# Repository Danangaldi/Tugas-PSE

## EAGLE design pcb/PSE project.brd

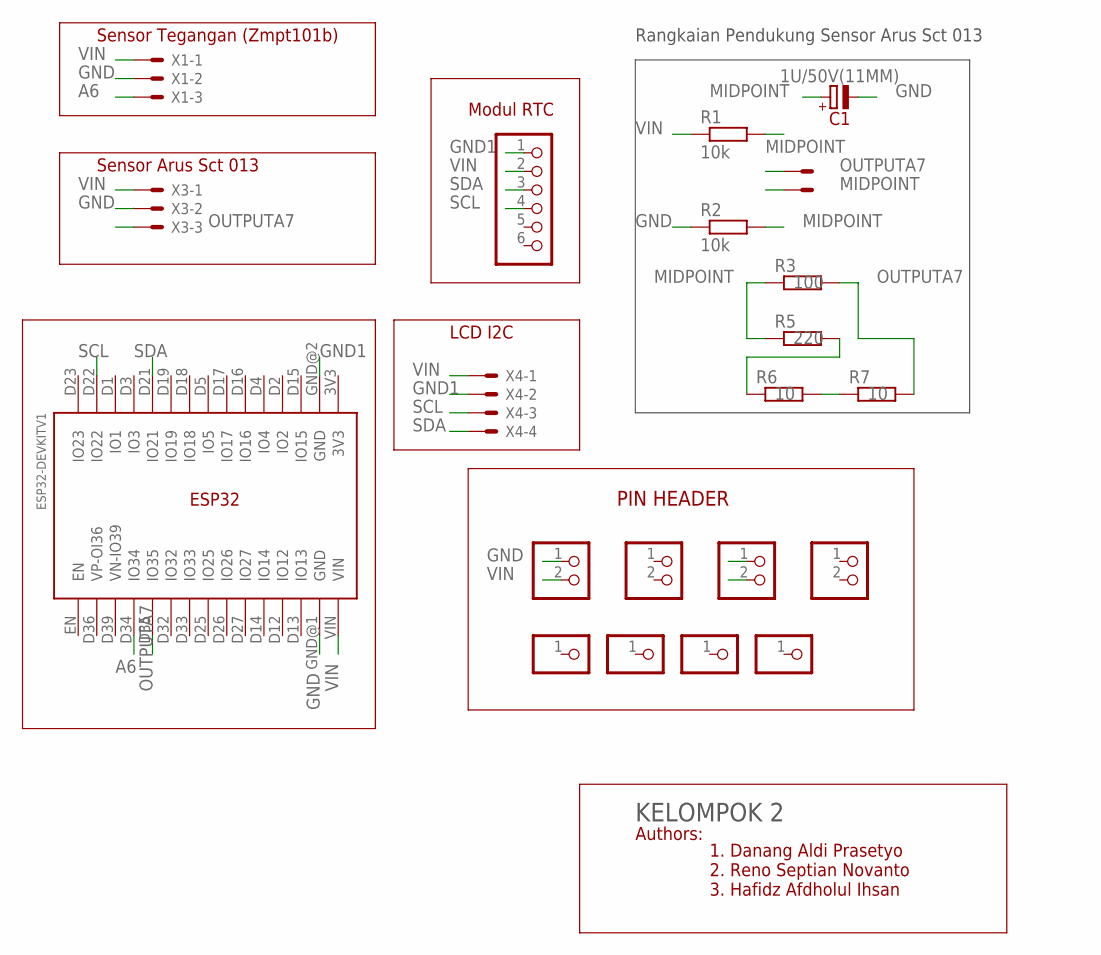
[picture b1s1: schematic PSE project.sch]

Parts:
C1: 1U/50V(11MM); E2-5
JP1, JP2, JP3, JP4: PINHD-1X2; 1X02
JP5: PINHD-1X6; 1X06
JP6, JP7, JP8, JP9: PINHD-1X1; 1X01
R1, R2: 10k; 0204/5
R3: 100; 0204/5
R5: 220; 0204/5
R6, R7: 10; 0204/5
U$1: ESP32DEVKITV1; ESP32-DEVKITV1
X1, X3: JST-XH-03-PIN-LONG-PAD; JST-XH-03-PACKAGE-LONG-PAD
X4: JST-XH-04-PIN-LONG-PAD; JST-XH-04-PACKAGE-LONG-PAD
X7: JST-XH-02-PIN-LONG-PAD; JST-XH-02-PACKAGE-LONG-PAD

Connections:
A6: U$1.D34 (IO34), X1.3
GND: C1.-, JP1.1, R2.1, U$1.GND@1 (GND), X1.2, X3.2
GND1: JP5.1, U$1.GND@2 (GND), X4.2
MIDPOINT: C1.+, R1.2, R2.2, R3.1, R5.1, X7.2
unnamed: R6.2, R7.1
unnamed: R5.2, R6.1
OUTPUTA7: R3.2, R7.2, U$1.D35 (IO35), X3.3, X7.1
SCL: JP5.4, U$1.D22 (IO22), X4.3
SDA: JP5.3, U$1.D21 (IO21), X4.4
VIN: JP1.2, JP5.2, R1.1, U$1.VIN, X1.1, X3.1, X4.1

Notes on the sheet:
Sensor Tegangan (Zmpt101b)
Sensor Arus Sct 013
Rangkaian Pendukung Sensor Arus Sct 013
Modul RTC
LCD I2C
PIN HEADER
ESP32
KELOMPOK 2
1. Danang Aldi Prasetyo 2. Reno Septian Novanto 3. Hafidz Afdholul Ihsan
Authors:

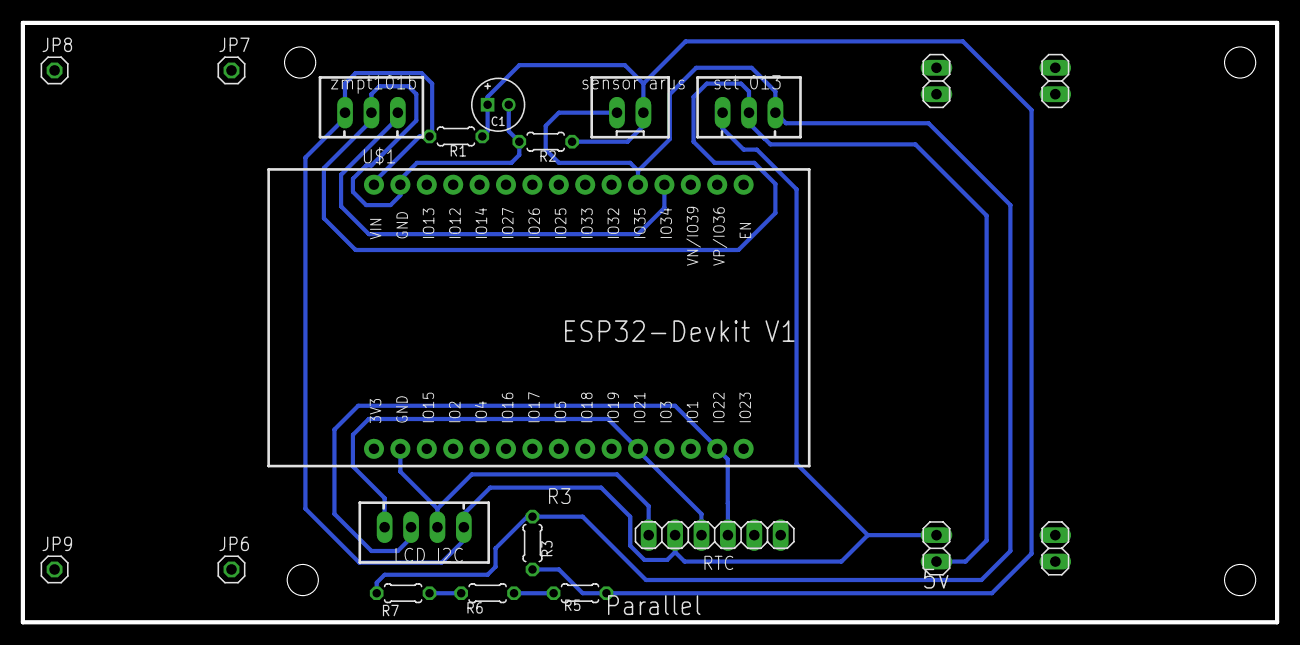
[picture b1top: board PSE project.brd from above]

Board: 2 copper layers, 120.7 x 57.7 mm, 21 parts (0 on the bottom side), 10 nets.

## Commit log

2023-05-27 semester 6
